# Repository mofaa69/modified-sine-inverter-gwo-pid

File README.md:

# Metasezgisel Algoritma Tabanlı Modifiye Sinüs Evirici (Inverter) Tasarımı

Bu proje, **TÜBİTAK 2209-A Üniversite Öğrencileri Araştırma Projeleri Destekleme Programı** (Proje No: 1919B012454606) kapsamında **Karadeniz Teknik Üniversitesi Elektrik-Elektronik Mühendisliği Bölümü**'nde tamamlanmış lisans bitirme çalışmasıdır.

---

## 📌 Proje Özeti
Bu çalışmada, 24V DC giriş gerilimini 12V-18V RMS 50Hz AC çıkış gerilimine dönüştüren, 180W maksimum güce sahip kapalı çevrim bir modifiye sinüs evirici sistemi tasarlanmış ve prototipi üretilmiştir. Sistemin güç hatları pcb üzerinde yapılmamış olup 1.5mm çok damarlı kablolar ile hibrit bir şekilde yapılmıştır.PCB üzerinde mikrokontrolcü yuvası tasarımı Attiny85 için yapılmıştır ancak kolaylıkla arduino mikrokontrolcülerle beraber de kullanılabilir.

Çıkış geriliminin kararlılığını sağlamak için Arduino tabanlı bir **PID denetleyici** kurgulanmış; PID kontrolörün Kp ve Ki parametreleri metasezgisel bir sürü zekası algoritması olan **Gri Kurt Optimizasyonu (GWO)** ile optimize edilmiştir.

---

## 🛠️ Donanım & Sistem Mimarisi

* **Güç Katı & Topoloji:** 24V DC beslemeli, 4 adet **IRLZ44N MOSFET** ile kurgulanmış H-Köprüsü (H-Bridge) topolojisi.
* **Sürücü Katı & Bootstrap:** High-side MOSFET tetikleme problemini çözmek amacıyla **IR2110** sürücü entegreleri ve 47µF/25V kondansatör + UF4007 hızlı diyottan oluşan **Bootstrap (Yüzer Kaynak)** mimarisi.
* **Mikrodenetleyici:** Arduino Uno R3 (ATmega328P) — Donanımsal Timer kesmeleri (Timer1 ISR) kullanılarak 50Hz Hassas PWM sinyali üretimi.
* **Geri Besleme & Sensör:** Tam dalga diyot köprüsü (UF4007), $22k\Omega / 4.7k\Omega$ gerilim bölücü ve 10µF filtre kapasitöründen oluşan feedback devresi.
* **Kullanıcı Arayüzü:** I2C modüllü 16x2 LCD ekran ve potansiyometre ile 12V–18V arası anlık referans gerilimi ayarlama.

---

## 📊 Simülasyon ve Optimizasyon (GWO)

* **MATLAB / Simulink:** H-Köprüsü güç katı, yük değişimleri ve batarya voltaj düşümü senaryoları altında kapalı çevrim olarak simüle edilmiştir.
* **Gri Kurt Optimizasyonu (GWO):** Simulink modeliyle entegre çalışan MATLAB algoritması sayesinde minimum hata kriterine göre en ideal kontrolör parametreleri tespit edilmiştir.

---

## 📁 Depo İçeriği

* **`/pcb`**: Şematik çizimler, PCB layout ve 3D kart modelleri.
* **`/simülasyon`**: GWO optimizasyon `.m` kodları ve kapalı çevrim Simulink (`.slx`) modeli.
* **`/yazılım`**: Timer kesmeli, I2C ekran destekli ve anlık PI kontrol hesaplamalı C++ / Arduino kodları.
* **`/proje raporu`**: KTÜ Bitirme Projesi nihai raporu (PDF).

---

## 🔬 Laboratuvar & Deneysel Sonuçlar
Fiziksel olarak üretilen baskı devre (PCB) üzerinde yapılan testlerde, 8.2Ω / 4A yük altında 12.00V ve 18.03V True RMS çıkış değerleri elde edilmiş, simülasyon sonuçları ile deneysel verilerin tam uyum sağladığı doğrulanmıştır.

---

## 🛠️ Kullanılan Teknolojiler
`KiCad` | `MATLAB / Simulink` | `Arduino IDE` | `C/C++` | `GWO Algorithm` | `PID Control`

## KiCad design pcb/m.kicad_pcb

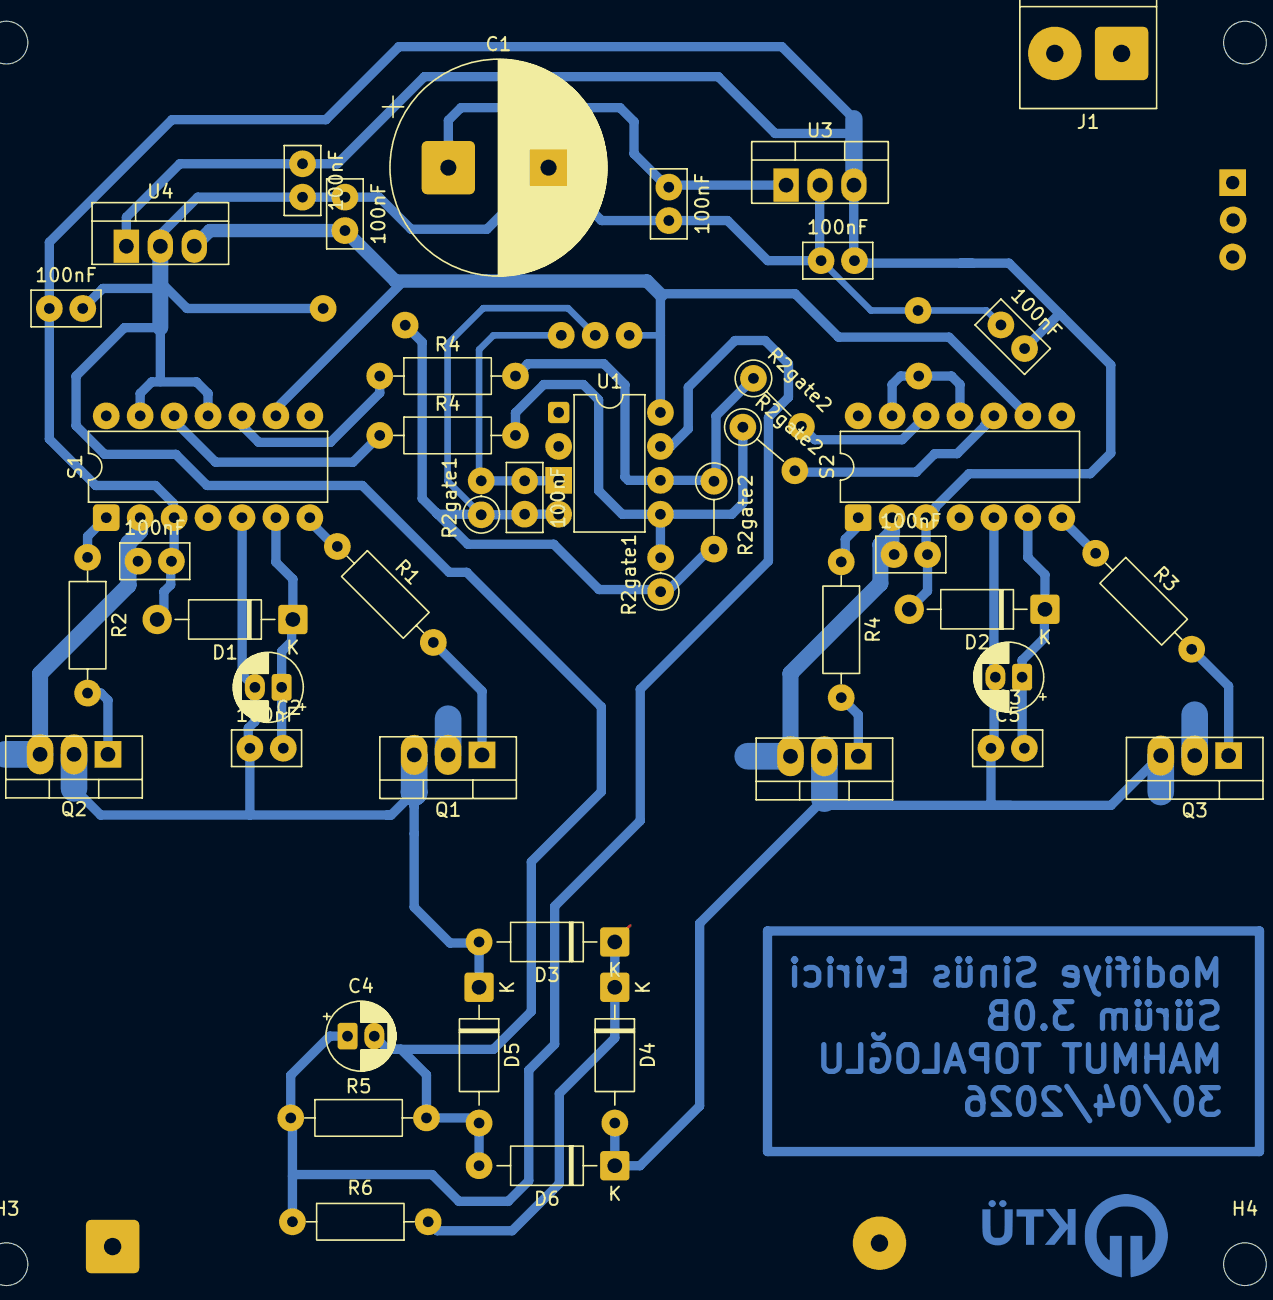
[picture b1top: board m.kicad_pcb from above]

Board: 2 copper layers, 48 parts (0 on the bottom side), 21 nets.

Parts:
100nF, 100nF#2, 100nF#3, 100nF#4, 100nF#5, 100nF#6, 100nF#7, 100nF#8, 100nF#9, 100nF#10: C; C_Disc_D5.0mm_W2.5mm_P2.50mm
C1: 2.2mF; CP_Radial_D16.0mm_P7.50mm
C2, C3: 47uF; CP_Radial_D5.0mm_P2.00mm
C4: 10uF; CP_Radial_D5.0mm_P2.00mm
C5: C; C_Disc_D5.0mm_W2.5mm_P2.50mm
D1, D2, D3, D4, D5, D6: UF4007; D_DO-41_SOD81_P10.16mm_Horizontal
H1, H2, H3, H4: MountingHole; MountingHole_3.2mm_M3
J1: Batarya; TerminalBlock_Phoenix_PT-1,5-2-5.0-H_1x02_P5.00mm_Horizontal
Q1, Q2, Q3, Q4: IRLZ44N; TO-220-3_Vertical
R1, R2, R3, R4: 22R; R_Axial_DIN0207_L6.3mm_D2.5mm_P10.16mm_Horizontal
R2gate1: 100K; R_Axial_DIN0207_L6.3mm_D2.5mm_P2.54mm_Vertical
R2gate1#2: 10K; R_Axial_DIN0207_L6.3mm_D2.5mm_P2.54mm_Vertical
R2gate2, R2gate2#2, R2gate2#3: 220R; R_Axial_DIN0207_L6.3mm_D2.5mm_P5.08mm_Vertical
R4#2, R4#3: 220R; R_Axial_DIN0207_L6.3mm_D2.5mm_P10.16mm_Horizontal
R5: 4.7K; R_Axial_DIN0207_L6.3mm_D2.5mm_P10.16mm_Horizontal
R6: 22K; R_Axial_DIN0207_L6.3mm_D2.5mm_P10.16mm_Horizontal
S1, S2: IR2110; DIP-14_W7.62mm
U1: ATtiny85V-10P; DIP-8_W7.62mm
U3: LM7812_TO220; TO-220-3_Vertical
U4: LM7805_TO220; TO-220-3_Vertical

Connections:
/5V: 100nF#3.2, S1.9 (VDD), S2.9 (VDD), U1.8 (VCC), U4.3 (VO)
/12V: 100nF.1, 100nF#2.1, 100nF#6.2, 100nF#7.2, 100nF#9.2, 100nF#10.2, D1.2 (A), D2.2 (A), S1.3 (VCC), S2.3 (VCC), U3.3 (VO), U4.1 (VI)
/GND: 100nF.2, 100nF#2.2, 100nF#3.1, 100nF#4.2, 100nF#6.1, 100nF#7.1, 100nF#8.2, 100nF#9.1, 100nF#10.1, C1.2, C4.2, D5.2 (A), D6.2 (A), J1.1, Q2.3 (S), Q4.3 (S), R2gate1.1, R2gate1#2.1, R2gate2#3.2, R5.2, S1.2 (COM), S1.11 (SD), S1.13 (VSS), S2.2 (COM), S2.11 (SD), S2.13 (VSS), U1.4 (GND), U3.2 (GND), U4.2 (GND)
/Guc: 100nF#4.1, C1.1, J1.2, Q1.2 (D), Q3.2 (D), U3.1 (VI)
/L: 100nF#5.1, C2.2, D3.2 (A), D5.1 (K), Q1.3 (S), Q2.2 (D), S1.5 (VS)
/N: C3.2, D4.2 (A), D6.1 (K), Q3.3 (S), Q4.2 (D), S2.5 (VS)
/Sinyal1: R2gate1#2.2, R2gate2#2.1, R2gate2#2.2, R4#2.1, R4#2.2, S1.12 (LIN), S2.10 (HIN), U1.5 (AREF/PB0)
/Sinyal2: R2gate2.1, R2gate2.2, R2gate2#3.1, R4#3.1, R4#3.2, S1.10 (HIN), S2.12 (LIN), U1.6 (PB1)
unnamed: 100nF#5.2, C2.1, D1.1 (K), S1.6 (VB)
unnamed: C3.1, D2.1 (K), S2.6 (VB)
unnamed: D3.1 (K), D4.1 (K), R6.1
unnamed: Q1.1 (G), R1.2
unnamed: Q2.1 (G), R2.2
unnamed: Q3.1 (G), R3.2
unnamed: Q4.1 (G), R4.2
unnamed: R1.1, S1.7 (HO)
unnamed: R2.1, S1.1 (LO)
unnamed: R3.1, S2.7 (HO)
unnamed: R4.1, S2.1 (LO)
unnamed: C4.1, R5.1, R6.2, U1.7 (PB2)
unnamed: 100nF#8.1, R2gate1.2, U1.3 (XTAL2/PB4)
